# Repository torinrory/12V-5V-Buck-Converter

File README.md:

# 12V-to-5V 3A Synchronous DC-DC Buck Converter (TPS54302)

**Author:** Torin Hamilton  
**CAD Tool:** KiCad 10.0  
**Topology:** Fixed-Frequency ($400\text{ kHz}$) Peak-Current-Mode Synchronous Buck Converter  
**Board Dimensions:** $45\text{ mm} \times 30\text{ mm}$, 2-Layer FR-4 ($1.6\text{ mm}$ thickness, $1\text{ oz}$ copper)

*Rev 1.1 (3D render).*

*Rev 1.1 (2D layout).*

<details>
<summary>Rev 1.0 renders (first PCB, as fabricated)</summary>

</details>

## Revision History

| Rev | Status | Summary |
| :-: | :--- | :--- |
| **1.0** | PCBs and components ordered; awaiting assembly and bring-up | First PCB design. Component values follow TI's 5 V, 3 A reference design (Datasheet Figure 7-1). Post-layout review findings are documented in [Section 6](#6-known-issues--rev-11-changes). |
| **1.1** | PCBs ordered from OSH Park and components ordered from Mouser (Nov 2026); awaiting assembly and bring-up | Addresses all eight Rev 1.0 issues in [Section 6](#6-known-issues--rev-11-changes): shortened input hot loop with dedicated `GND` vias, solid SMD ground connections and 32 `GND` stitching vias, input damping capacitor `C7`, compact feedback network, extended `L1` pad, reduced `SW` copper, and Keystone-compatible test points. |

---

## 1. Project Overview

This project implements a compact, high-efficiency **12V-to-5V, 3A Synchronous Step-Down (Buck) DC-DC Converter** based on the Texas Instruments **`TPS54302`** (`SOT-23-6`). It is designed for 12V/24V distributed power buses, embedded systems, and benchtop prototyping, with all surface-mount and through-hole footprints selected and spaced for reliable hand-soldering and oscilloscope characterization.

### Key Electrical Specifications

| Parameter | Symbol | Value | Notes |
| :--- | :---: | :---: | :--- |
| **Input Voltage Range** | $V_{\text{IN}}$ | $8\text{ V} \text{ to } 28\text{ V}$ | Optimized for $12\text{ V}$ nominal; matches TI reference design (Datasheet Table 7-1) |
| **Output Voltage** | $V_{\text{OUT}}$ | $5.08\text{ V}$ ($5.0\text{ V}$ nom) | Set by $1\%$ feedback divider ($R_2, R_3$); $\approx 4.9\text{ -- } 5.25\text{ V}$ worst case over $V_{\text{ref}}$ ($0.581\text{ -- }0.611\text{ V}$) and resistor tolerance |
| **Max Continuous Output Current** | $I_{\text{OUT(MAX)}}$ | $3.0\text{ A}$ | Integrated $85\text{ m}\Omega$ HS / $40\text{ m}\Omega$ LS MOSFETs |
| **Switching Frequency** | $f_{\text{SW}}$ | $400\text{ kHz}$ | With $\pm 6\%$ frequency spread-spectrum for EMI reduction |
| **Peak Efficiency** | $\eta$ | $\approx 93\% \text{ -- } 95\%$ | At $V_{\text{IN}} = 12\text{ V}, V_{\text{OUT}} = 5\text{ V}$ |
| **Output Voltage Ripple** | $\Delta V_{\text{OUT}}$ | $< 30\text{ mV}_{\text{PP}}$ | Low-ESR MLCC output filter ($2 \times 22\,\mu\text{F}$) |
| **Transient Response ($1.5\text{ A}$ step)** | $\Delta V_{\text{TR}}$ | $< \pm 5\%$ ($\pm 250\text{ mV}$) | Phase-margin boosted via $75\text{ pF}$ feedforward cap |

### Repository Contents
- **[fab/rev1.0/](fab/rev1.0/)** — Rev 1.0 fabrication snapshot, exactly as ordered:
  - [Schematic PDF](fab/rev1.0/12V_5V_Buck_Converter_rev1.0_schematic.pdf) with engineering callouts
  - [Gerber & drill package (.zip)](fab/rev1.0/12V_5V_Buck_Converter_rev1.0_gerbers.zip) and [individual files](fab/rev1.0/gerbers/) (RS-274X Gerbers, Excellon drill)
  - [BOM as ordered](fab/rev1.0/12V_5V_Buck_Converter_rev1.0_BOM.xlsx)
- **[fab/rev1.1/](fab/rev1.1/)** — Rev 1.1 fabrication package:
  - [Schematic PDF](fab/rev1.1/12V_5V_Buck_Converter_rev1.1_schematic.pdf)
  - [Gerber & drill package (.zip)](fab/rev1.1/12V_5V_Buck_Converter_rev1.1_gerbers.zip) and [individual files](fab/rev1.1/gerbers/) (RS-274X Gerbers, Excellon drill)
  - [BOM](fab/rev1.1/12V_5V_Buck_Converter_rev1.1_BOM.xlsx)
- **KiCad source (always the latest revision; currently Rev 1.1):**
  - [12V_5V_Buck_Converter.kicad_sch](12V_5V_Buck_Converter.kicad_sch): KiCad 10 schematic (Rev 1.0 passed with 0 ERC violations)
  - [12V_5V_Buck_Converter.kicad_pcb](12V_5V_Buck_Converter.kicad_pcb): KiCad 10 2-layer PCB layout (0 DRC violations)
  - [Library.pretty/](Library.pretty/) + [fp-lib-table](fp-lib-table): project footprint library (`L1` extended-pad footprint)
- **[BOM.xlsx](BOM.xlsx)** — Current (Rev 1.1) orderable Bill of Materials with Manufacturer Part Numbers; the Rev 1.0 order record is kept on a separate sheet
- **[images/](images/)** — PCB renders, named by revision
- **[docs/](docs/)** — Reference datasheets (TI TPS54302)

---

## 2. Engineering Design & Component Calculations

All component values are derived from the [Texas Instruments TPS54302 Datasheet](docs/tps54302.pdf) (Section 7.2, Pages 14–18).

### 2.1 Output Voltage Set Point ($R_2, R_3$)
The `TPS54302` regulates the feedback pin (`FB`, Pin 4) to an internal bandgap reference of $V_{\text{ref}} = 0.596\text{ V}$ (typical). Using $R_2 = 100\text{ k}\Omega$ ($1\%$) for the upper divider resistor and $R_3 = 13.3\text{ k}\Omega$ ($1\%$) for the lower divider resistor:

$$V_{\text{OUT}} = V_{\text{ref}} \times \left(1 + \frac{R_2}{R_3}\right) = 0.596\text{ V} \times \left(1 + \frac{100\text{ k}\Omega}{13.3\text{ k}\Omega}\right) = 5.077\text{ V}$$

A $49.9\,\Omega$ resistor ($R_1$) is placed in series between $V_{\text{OUT}}$ and the top of the feedback network to provide an injection point for control-loop Bode plot / stability measurements.

### 2.2 Programmable Input Undervoltage Lockout ($R_4, R_5$)
Resistors $R_4 = 511\text{ k}\Omega$ ($1\%$) and $R_5 = 105\text{ k}\Omega$ ($1\%$) form an external voltage divider on the `EN` pin (Pin 5) working with the internal pull-up current ($I_p = 0.7\,\mu\text{A}$) and hysteresis current ($I_h = 1.55\,\mu\text{A}$) to prevent brownout chatter during startup and shutdown:
- **Rising Turn-On Threshold ($V_{\text{EN(rising)}} = 1.23\text{ V}$):**
  $$V_{\text{START}} = V_{\text{EN(rising)}} \left(1 + \frac{R_4}{R_5}\right) - I_p R_4 \approx 6.86\text{ V}$$
- **Falling Turn-Off Threshold ($V_{\text{EN(falling)}} = 1.16\text{ V}$):**
  $$V_{\text{STOP}} = V_{\text{EN(falling)}} \left(1 + \frac{R_4}{R_5}\right) - (I_p + I_h) R_4 \approx 5.65\text{ V}$$

### 2.3 Output Inductor Selection ($L_1$)
For a target inductor ripple ratio $K_{\text{IND}} = 0.35$ up to $V_{\text{IN(MAX)}} = 28\text{ V}$ at $f_{\text{SW}} = 400\text{ kHz}$:

$$L_{\text{MIN}} = \frac{V_{\text{OUT}} \times (V_{\text{IN(MAX)}} - V_{\text{OUT}})}{V_{\text{IN(MAX)}} \times K_{\text{IND}} \times I_{\text{OUT}} \times f_{\text{SW}}} = \frac{5 \times (28 - 5)}{28 \times 0.35 \times 3 \times 400\times 10^3} = 9.78\,\mu\text{H}$$

Selecting the standard value **$L_1 = 10\,\mu\text{H}$** (`Bourns SRP7028A-100M`):
- **Inductor Ripple Current at $V_{\text{IN}} = 12\text{ V}$:**
  $$\Delta I_L = \frac{V_{\text{OUT}} \times (V_{\text{IN}} - V_{\text{OUT}})}{V_{\text{IN}} \times L_1 \times f_{\text{SW}}} = \frac{5 \times (12 - 5)}{12 \times 10\,\mu\text{H} \times 400\text{ kHz}} = 0.729\text{ A}_{\text{PP}}$$
- **Peak Inductor Current ($I_{L(\text{PK})}$):**
  $$I_{L(\text{PK})} = I_{\text{OUT(MAX)}} + \frac{\Delta I_L}{2} \approx 3.36\text{ A} \quad (\text{ at } 12\text{ V}) \quad / \quad 3.51\text{ A} \quad (\text{ at } 28\text{ V})$$
- **Selected Inductor Margins:** The `Bourns SRP7028A-100M` shielded power inductor is rated for **$I_{\text{RMS}} = 3.5\text{ A}$** and **$I_{\text{sat}} = 6.0\text{ A}$** (DCR $75\text{ m}\Omega$ typ / $85\text{ m}\Omega$ max, Bourns datasheet). That gives about $1.7\times$ saturation margin over the $3.51\text{ A}$ worst-case peak current (at $28\text{ V}$ input) and about $17\%$ headroom between the $3.5\text{ A}$ RMS rating and the $3.0\text{ A}$ maximum continuous output current.

### 2.4 Input & Output Capacitor Selection ($C_1\text{--}C_7$)
- **Input Decoupling ($C_1 = 10\,\mu\text{F}, 50\text{ V}$ & $C_2 = 0.1\,\mu\text{F}, 50\text{ V X7R}$):**
  - Worst-case input RMS ripple current is $I_{\text{CIN(RMS)}} \approx I_{\text{OUT(MAX)}} / 2 = 1.5\text{ A}$.
  - $C_1$ ($1206$ package, $50\text{ V}$ X5R/X7R) provides bulk charge storage with minimal DC-bias derating at $12\text{ V}$, while $C_2$ ($0805$) is placed immediately adjacent to `U1` Pin 3 (`VIN`) and Pin 1 (`GND`) to shunt high-$di/dt$ switching currents.
- **Input Damping Capacitor ($C_7 = 47\,\mu\text{F}, 50\text{ V}$ aluminum electrolytic, added in Rev 1.1):**
  - Ceramic-only input capacitance and the supply-lead inductance form a lightly damped LC that can ring toward $2 \times V_{\text{IN}}$ when the board is connected to a live supply. `C7` provides roughly $6\times$ the effective ceramic input capacitance, and its ESR ($\sim 0.5\text{ -- }1\,\Omega$, comparable to the LC characteristic impedance) damps the ringing. At $400\text{ kHz}$ the switching ripple still flows almost entirely through the ceramics.
- **Bootstrap Capacitor ($C_3 = 0.1\,\mu\text{F}, 50\text{ V X7R}$):**
  - Connected between `BOOT` (Pin 6) and `SW` (Pin 2) to supply the floating gate drive for the integrated high-side N-channel MOSFET.
- **Output Filter Capacitors ($C_4, C_5 = 2 \times 22\,\mu\text{F}, 25\text{ V X5R/X7R}$):**
  - To contain a $1.5\text{ A}$ load transient within $\Delta V_{\text{OUT}} = \pm 5\%$ ($0.25\text{ V}$), the minimum required effective output capacitance is:
    $$C_{\text{OUT(MIN)}} > \frac{2 \times \Delta I_{\text{OUT}}}{f_{\text{SW}} \times \Delta V_{\text{OUT}}} = \frac{2 \times 1.5\text{ A}}{400\text{ kHz} \times 0.25\text{ V}} = 30\,\mu\text{F}$$
  - Using two parallel $22\,\mu\text{F}$, $25\text{ V}$ `1206` ceramic capacitors ($44\,\mu\text{F}$ nominal) accounts for MLCC DC-bias derating at $5\text{ V}$ while halving equivalent series resistance (ESR) and ESL.
- **Feedforward Compensation Capacitor ($C_6 = 75\text{ pF}, 50\text{ V C0G/NP0}$):**
  - Placed in parallel with $R_2$ to introduce a phase-lead zero near the control loop crossover frequency ($f_0 \approx \frac{5.1}{V_{\text{OUT}} \times C_{\text{OUT}}} \approx 23\text{ kHz}$), boosting phase margin with low-ESR ceramic output capacitors:
    $$C_6 \approx \frac{1}{2\pi f_0 R_2} \approx 75\text{ pF}$$

---

## 3. PCB Layout & EMI Mitigation Architecture

Switching regulators involve high-$di/dt$ current loops ($400\text{ kHz}$ square-wave switching up to $3\text{ A}$). The 2-layer PCB ([12V_5V_Buck_Converter.kicad_pcb](12V_5V_Buck_Converter.kicad_pcb)) follows Texas Instruments' layout guidelines (Datasheet Section 7.4). This section describes the **Rev 1.1** layout; the Rev 1.0 layout and its issues are documented in [Section 6](#6-known-issues--rev-11-changes).

1. **Short Input Hot Loop:** `C2` ($0.1\,\mu\text{F}$) sits $\approx 2\text{ mm}$ from `U1` Pin 3 (`VIN`), with `C1` ($10\,\mu\text{F}$) directly behind it. Because the `SW` trace leaving Pin 2 must split the top-layer pour between the capacitors and Pin 1, the `GND` return is made through the bottom plane: three `GND` vias at the `C1`/`C2` ground pads and two at `U1` Pin 1 keep the loop to a few millimeters.
2. **Compact Switching Node (`SW`):** `L1` is rotated so its `SW` pad faces `U1`, and bootstrap capacitor `C3` sits directly on the `SW` path between `L1` and `U1` with a $\approx 3\text{ mm}$ `BOOT` trace to Pin 6. Test point `TP2` is a $1.5\text{ mm}$ top-layer pad on a $0.3\text{ mm}$ trace, so no high-current-width copper or plated hole is added to the `SW` node.
3. **High-Current Power Routing with Pin Neck-Down:** `Vin`, `SW`, and `Vout` use $1.5\text{ mm}$ tracks, necking down to $0.5\text{ mm}$ only for the last $\approx 1.5\text{ mm}$ into the fine-pitch ($0.95\text{ mm}$) `SOT-23-6` pads.
4. **Compact Feedback Network:** `R2`, `R3`, and `C6` are grouped at `U1` Pin 4 on the side away from `L1` and `SW`; the high-impedance `FB` node is entirely on `F.Cu` ($\approx 4\text{ mm}$ to `R3`, $4\text{ mm}$ across the divider). The longer run is on the low-impedance sense side: `R1` taps `Vout` at output capacitor `C4`.
5. **Output Filter Placement:** `L1` feeds `C4`/`C5` before the output connector `J2`, so the load sees filtered output.
6. **Input Damping:** Electrolytic `C7` sits in-line on the `Vin` trace between `J1` and the ceramic input capacitors.
7. **Ground Planes, Vias & Thermal Path:** Both `F.Cu` and `B.Cu` are poured with `GND` (`0.3 mm` clearance). SMD pads connect solidly to the pour (zone setting *Reliefs for PTH*) for low inductance and heat spreading from `U1`; through-hole pads keep thermal reliefs for hand soldering. 32 `GND` vias, at the critical capacitor and IC ground pads plus a $\approx 6\text{ mm}$ stitching pattern, tie the layers together. The bottom plane is unbroken under the power stage.
8. **Test Points:** `TP1` (`Vin`), `TP3` (`Vout`), and `TP4` (`GND`) use Keystone 5005 compact loops ($1.6\text{ mm}$ holes). `TP4` sits $4\text{ mm}$ from `TP3` for a scope ground-spring ripple measurement.

---

## 4. Bill of Materials (BOM)

The full Rev 1.1 spreadsheet is available in [BOM.xlsx](BOM.xlsx) (the Rev 1.0 order record is on its own sheet and in [fab/rev1.0/](fab/rev1.0/)).

| Ref | Qty | Value | Package | Manufacturer | MPN | Description |
| :--- | :-: | :--- | :--- | :--- | :--- | :--- |
| `U1` | 1 | `TPS54302` | `SOT-23-6` | Texas Instruments | `TPS54302DDCT` | 4.5V–28V In, 3A Sync Buck Converter (`DDCR` is the same part on a larger reel) |
| `L1` | 1 | `10uH` | `7.3x6.6mm` | Bourns | `SRP7028A-100M` | Shielded Power Inductor, $3.5\text{ A}_{\text{RMS}}$, $6\text{ A}_{\text{sat}}$, $85\text{ m}\Omega$ max DCR (custom footprint, `Vout` pad extended $1\text{ mm}$ for hand soldering) |
| `C1` | 1 | `10uF` | `1206` | Murata | `GRT31CR61H106KE01L` | MLCC $10\,\mu\text{F}$, $50\text{ V}$, X5R, $\pm 10\%$. **Rev 1.0 as built:** out-of-stock substitute Murata `GRM31CR71E106MA12L` ($25\text{ V}$) — see bench input-voltage limit in Section 5 |
| `C2, C3` | 2 | `0.1uF` | `0805` | Yageo | `CC0805KRX7R9BB104` | MLCC $0.1\,\mu\text{F}$, $50\text{ V}$, X7R, $\pm 10\%$ |
| `C4, C5` | 2 | `22uF` | `1206` | Samsung | `CL31A226KAHNNNE` | MLCC $22\,\mu\text{F}$, $25\text{ V}$, X5R, $\pm 10\%$ |
| `C6` | 1 | `75pF` | `0805` | Yageo | `CC0805JRNPO9BN750` | MLCC $75\text{ pF}$, $50\text{ V}$, C0G/NP0, $\pm 5\%$ |
| `C7` | 1 | `47uF` | Radial $8 \times 11\text{ mm}$, $3.5\text{ mm}$ pitch | KEMET | `ESH476M050AG3KA` | Aluminum electrolytic $47\,\mu\text{F}$, $50\text{ V}$, $105\,{}^{\circ}\text{C}$ — input damping (Rev 1.1) |
| `R1` | 1 | `49.9` | `0805` | Yageo | `RC0805FR-0749R9L` | Thick Film Resistor $49.9\,\Omega$, $1\%$, $1/8\text{ W}$ |
| `R2` | 1 | `100k` | `0805` | Yageo | `RC0805FR-07100KL` | Thick Film Resistor $100\text{ k}\Omega$, $1\%$, $1/8\text{ W}$ |
| `R3` | 1 | `13.3k` | `0805` | Yageo | `RC0805FR-0713K3L` | Thick Film Resistor $13.3\text{ k}\Omega$, $1\%$, $1/8\text{ W}$ |
| `R4` | 1 | `511k` | `0805` | Yageo | `RC0805FR-07511KL` | Thick Film Resistor $511\text{ k}\Omega$, $1\%$, $1/8\text{ W}$ |
| `R5` | 1 | `105k` | `0805` | Yageo | `RC0805FR-07105KL` | Thick Film Resistor $105\text{ k}\Omega$, $1\%$, $1/8\text{ W}$ |
| `R6` | 1 | `1k` | `0805` | Yageo | `RC0805FR-071KL` | Thick Film Resistor $1\text{ k}\Omega$, $1\%$, $1/8\text{ W}$ |
| `D1` | 1 | `Green` | `0805` | Lite-On | `LTST-C170KGKT` | Green SMD LED ($571\text{ nm}, V_F = 2.0\text{ V}$) |
| `J1, J2` | 2 | `Screw Term` | `1x02 P5.08mm` | Phoenix Contact | `1715721` | 2-Pin Terminal Block, $5.08\text{ mm}$, $17.5\text{ A}$ |
| `TP1, TP3, TP4` | 3 | `Test Point` | Keystone compact, $1.6\text{ mm}$ hole | Keystone | `5005` | Compact test point loop (`Vin`, `Vout`, `GND`) |
| `TP2` | — | `Test Pad` | $1.5\text{ mm}$ SMD pad | — | DNP (bare pad) | `SW` probe point; no part installed |

---

## 5. Hand-Soldering & Bench Bring-Up Guide

### Recommended Soldering Order (Lowest to Highest Profile)
1. **Regulator IC (`U1` - `TPS54302`):** Verify the Pin 1 dot/bevel aligns with the top-left pad (`GND`, marked by the silkscreen triangle). Tack one corner pin with flux and fine solder, verify alignment, then solder the remaining 5 pins.
2. **0805 Passives & LED (`C2`, `C3`, `C6`, `R1`–`R6`, `D1`):** Note that `D1` is polarized—align the green cathode marking on the LED with **Pad 1 (`GND`, left pad)**.
3. **1206 Input/Output Capacitors (`C1`, `C4`, `C5`).**
4. **Power Inductor (`L1` - `SRP7028A-100M`):** Pre-tin both pads. Place `L1`, then heat the extended `Vout` pad (Rev 1.1) with the iron until the solder underneath reflows and the part seats. Reflow the `SW` side with hot air, or with the iron and flux on the exposed pad edge.
5. **Through-Hole Parts (`J1`, `J2`, `C7`, `TP1`, `TP3`, `TP4`):** These pads tie into two layers of `GND` pour — raise the iron temperature and allow extra dwell time on the `GND` pins. `C7` is polarized: its `+` lead goes to the square pad (`Vin`).

### Bench Equipment
Bring-up and characterization use only a **current-limited bench DC power supply** and a **digital multimeter (DMM)**. Load is provided by a resistor load bank: six TE Connectivity `SQPW1010RJ` ($10\,\Omega$, $10\text{ W}$ axial wirewound) resistors on a TE/Buchanan `1546671-8` 8-position dual-row barrier strip. Alternate positions are tied together with 18 AWG jumpers to form `Vout` and `GND` buses, and each resistor bridges two adjacent positions. Each connected resistor adds $0.5\text{ A}$ at $5\text{ V}$ ($2.5\text{ W}$ per resistor); all six give $1.67\,\Omega$ = $3\text{ A}$. Connect it to `J2` with 18–20 AWG leads, and keep the hot resistor bodies clear of the plastic strip.

> **⚠ Rev 1.0 input-voltage limit:** The Rev 1.0 build uses a $25\text{ V}$-rated substitute for `C1` (the specified $50\text{ V}$ part was out of stock; Rev 1.1 specifies a $50\text{ V}$ part). Limit bench testing to **$\leq 15\text{ V}$ input** until `C1` is replaced with a $50\text{ V}$ $10\,\mu\text{F}$ capacitor. The $24\text{ V}$ and $28\text{ V}$ rows in the Section 5.5 results table apply only after that replacement.

### 5.1 Power-Off Checks
| Measurement (DMM) | Expected | Fault Indication |
| :--- | :--- | :--- |
| `J1` resistance (`Vin` to `GND`) | Rises as `C1` charges, settles in the hundreds of kΩ ($R_4 + R_5 \approx 616\text{ k}\Omega$) | $< 100\,\Omega$ → solder bridge / reversed part |
| `J2` resistance (`Vout` to `GND`) | $\approx 113\text{ k}\Omega$ ($R_1 + R_2 + R_3$), may read lower through `D1` | $< 100\,\Omega$ → solder bridge |
| `TP2` (`SW`) diode mode to `GND` and to `Vin` | One diode drop ($\approx 0.3\text{ -- }0.7\text{ V}$) in one direction | $\approx 0\text{ V}$ → `SW` shorted |
| `D1` diode mode | LED glows faintly | No glow → `D1` reversed or open |

### 5.2 No-Load Power-Up
1. Set the supply to **$12.0\text{ V}$** with a **$100\text{ mA}$** current limit and connect to `J1`.
2. `D1` should illuminate after the internal $5\text{ ms}$ soft start.
3. Input current should be only a few mA — mostly the LED ($\approx 3\text{ mA}$ at $5\text{ V}$ out, $\approx 1.5\text{ mA}$ at $12\text{ V}$ in), since Eco-mode pulse skipping keeps quiescent losses low.
4. `TP3` (`Vout`) to `TP4` (`GND`) should read **$\approx 4.9\text{ -- }5.25\text{ V}$** ($5.08\text{ V}$ nominal). Record the actual value; a reading anywhere in this window is within datasheet tolerance.

### 5.3 UVLO Threshold Verification
1. Starting at $0\text{ V}$, slowly raise the supply while monitoring `Vout`. Record the input voltage at which the output turns on (**expected $\approx 6.86\text{ V}$**).
2. Slowly lower the supply and record the input voltage at which the output drops out (**expected $\approx 5.65\text{ V}$**).

### 5.4 Switching Frequency (DMM Hz mode)
With $\geq 0.5\text{ A}$ of load applied (Eco-mode pulse skipping makes light-load readings low or unstable), measure `TP2` (`SW`) to `GND` in frequency mode. Expect **$\approx 400\text{ kHz}$**, varying by up to $\pm 6\%$ due to spread spectrum.

### 5.5 Load Regulation, Line Regulation & Efficiency
1. Raise the supply current limit to **$2.0\text{ A}$**.
2. Measure `Vout` directly across `C4`/`C5` (not at the load resistors) and `Vin` at `TP1`/`TP4`. Measure $I_{\text{OUT}}$ on the DMM's 10 A range in series with the load (or compute $V_{\text{OUT}} / R_{\text{LOAD}}$) and take $I_{\text{IN}}$ from the supply readout or DMM.
3. Step the load in $0.5\text{ A}$ increments at $V_{\text{IN}} = 8, 12, 24, 28\text{ V}$ and compute $\eta = \dfrac{V_{\text{OUT}} I_{\text{OUT}}}{V_{\text{IN}} I_{\text{IN}}}$.
4. Allow `U1` to settle thermally at each step above $2\text{ A}$. At $3\text{ A}$ the IC dissipates $\approx 0.6\text{ -- }0.7\text{ W}$; with $R_{\theta JA}$ between $57\,{}^{\circ}\text{C/W}$ (TI EVM) and $119\,{}^{\circ}\text{C/W}$ (JEDEC), a $50\text{ -- }80\,{}^{\circ}\text{C}$ rise is expected. If the output cycles off at full load, suspect thermal shutdown ($160\,{}^{\circ}\text{C}$).

| $V_{\text{IN}}$ (V) | $I_{\text{IN}}$ (A) | $V_{\text{OUT}}$ (V) | $I_{\text{OUT}}$ (A) | $P_{\text{IN}}$ (W) | $P_{\text{OUT}}$ (W) | $\eta$ (%) |
| :---: | :---: | :---: | :---: | :---: | :---: | :---: |
| 12 | | | 0.0 | | | — |
| 12 | | | 0.5 | | | |
| 12 | | | 1.0 | | | |
| 12 | | | 1.5 | | | |
| 12 | | | 2.0 | | | |
| 12 | | | 2.5 | | | |
| 12 | | | 3.0 | | | |
| 8 | | | 3.0 | | | |
| 24 | | | 3.0 | | | |
| 28 | | | 3.0 | | | |

### 5.6 Short-Circuit / Hiccup Protection (Optional)
With the supply limited to $\approx 1\text{ A}$, short `J2`. Average input current should remain low as the device enters hiccup mode (shutdown after 512 overcurrent cycles, restart after 16,384 cycles). Remove the short and confirm `Vout` recovers automatically.

### 5.7 Output Ripple (Oscilloscope Required)
A DMM's AC mode lacks the bandwidth to measure $400\text{ kHz}$ ripple. If an oscilloscope is available, AC-couple a probe with a short ground spring and verify $< 30\text{ mV}_{\text{PP}}$ ripple. On **Rev 1.1**, place the probe tip on `TP3` (`Vout`) and the ground spring on `TP4` (`GND`), $4\text{ mm}$ apart. On **Rev 1.0**, `TP3` and `TP4` are too far apart, so probe directly across `C5`.

---

## 6. Known Issues & Rev 1.1 Changes

A post-layout review of Rev 1.0 (direct inspection of the `.kicad_pcb` copper, zone fills, and via placement) found the following. Component values match TI's 5 V, 3 A reference design (Datasheet Figure 7-1, Table 7-2) exactly; the items below concern PCB layout and operating practice. None are expected to prevent regulation at $12\text{ V}$ input; they affect switching-node ringing, EMI, and thermal margin.

**Status:** ✅ All eight issues are fixed in the Rev 1.1 layout. These are design changes that have not yet been fabricated or bench-verified.

| # | Status | Issue (Rev 1.0) | Impact | Rev 1.0 Bench Workaround | Rev 1.1 Change |
| :-: | :-: | :--- | :--- | :--- | :--- |
| 1 | ✅ | **Enlarged input hot loop.** The `SW` trace leaving Pin 2 splits the top `GND` pour between `C2` and `U1` Pin 1, leaving Pin 1 on a small isolated top-copper island tied to the bottom plane by one via. The bottom-layer `GND` trace intended to link them terminates under `C2`'s top-side pad with no via, so it connects nothing. The actual `C2` return path runs through `J1`'s `GND` pin or the `C5` via and back through the bottom plane — roughly $35\text{ mm}$ versus a target of $< 5\text{ mm}$. DRC does not flag this because the net is connected through the pours. | Increased `SW` ringing/overshoot and radiated EMI; reduced `SW` voltage margin at $24\text{ -- }28\text{ V}$ input ($30\text{ V}$ abs. max) | Solder a short insulated jumper wire from `C2`'s `GND` pad directly to `U1` Pin 1, passing over the solder-masked `SW` trace | Place `C2` directly across Pins 3 and 1 with its `GND` pad on the same copper as Pin 1; add `GND` vias at the `C2` and `C1` ground pads; route `SW` so it does not bisect the input `GND` return **Done:** `C2` moved to $\approx 2\text{ mm}$ from Pin 3; three `GND` vias at the `C1`/`C2` ground pads and two at `U1` Pin 1 give a return path of a few millimeters through the bottom plane. |
| 2 | ✅ | **Limited thermal path for `U1`.** `0.3 mm` thermal-relief spokes and only two board-wide `GND` vias restrict heat spreading from the `SOT-23-6` pins. | Higher junction temperature at $3\text{ A}$ ($\approx 0.6\text{ -- }0.7\text{ W}$ dissipation); possible thermal shutdown ($160\,{}^{\circ}\text{C}$) at full load | Step load gradually and monitor `U1` temperature; derate continuous current if the output cycles off | Solid (no-spoke) pad connections for `U1` `GND` and power-capacitor `GND` pads; add a via stitching array around `U1` and the input/output capacitors **Done:** zone pad connection set to *Reliefs for PTH* — all SMD `GND` pads connect solidly while through-hole pads keep reliefs for solderability; 32 `GND` vias (critical-pad vias plus $\approx 6\text{ mm}$ stitching) tie the planes together. |
| 3 | ✅ | **Hot-plug input overshoot.** Ceramic-only input capacitance with lead inductance forms an underdamped LC that can ring toward $2 \times V_{\text{IN}}$ when connected to a live supply. | Safe at $12\text{ V}$ ($\approx 24\text{ V}$ peak); can exceed the $30\text{ V}$ `VIN` absolute maximum at $\geq 16\text{ V}$ input | Connect leads first, then enable the supply output | Add a damping bulk aluminum electrolytic (e.g., $47\,\mu\text{F}$, $50\text{ V}$) at `J1` **Done:** `C7`, KEMET `ESH476M050AG3KA` ($47\,\mu\text{F}$, $50\text{ V}$ aluminum electrolytic), placed in-line on the `Vin` trace at `J1`. |
| 4 | ✅ | **Long `FB` trace.** The high-impedance `FB` node runs $\approx 10\text{ mm}$ with two vias before reaching `R2`/`C6`. | Low risk (routed clear of `SW`); increased noise pickup susceptibility | — | Place `R2`, `R3`, and `C6` immediately adjacent to Pin 4; keep `FB` on one layer **Done:** `R2`, `R3`, and `C6` grouped at Pin 4; `FB` routed entirely on `F.Cu`; the `B.Cu` jumper and both `FB` vias removed. The longer run is now the low-impedance `R1` sense trace from `C4`. |
| 5 | ✅ | **`L1` hand-solderability.** `SRP7028A` terminals sit mostly beneath the inductor body. | Difficult to solder with an iron alone | Use hot air or a hot plate; pre-tin pads | Use extended-pad footprint variant **Done:** custom project-library footprint with the `Vout` pad extended $1\text{ mm}$ outward (inner edge unchanged). The `SW` pad is left at standard size to avoid adding switching-node copper next to `C3`. |
| 6 | ✅ | **Excess `SW` copper area.** A $6.2\text{ mm} \times 1.5\text{ mm}$ `SW` branch runs to bootstrap cap `C3` (followed by a $5\text{ mm}$ `BOOT` return to Pin 6), and a $6.8\text{ mm} \times 1.5\text{ mm}$ stub runs to `TP2`. Neither carries significant current. | The `SW` node swings $0 \leftrightarrow V_{\text{IN}}$ at $400\text{ kHz}$; extra copper increases capacitively coupled and radiated EMI | — | Place `C3` directly beside `U1` between Pins 2 and 6 with short $0.3\text{ -- }0.5\text{ mm}$ traces; narrow the `TP2` stub to $0.3\text{ mm}$ or relocate `TP2` adjacent to `L1` Pad 1 **Done:** `L1` rotated so its `SW` pad faces `U1`; `C3` placed on the `SW` path between `L1` and `U1` ($\approx 3\text{ mm}$ `BOOT` trace); `TP2` changed to a $1.5\text{ mm}$ SMD pad on a $0.3\text{ mm}$ trace. |
| 7 | ✅ | **Long necked-down power traces.** `SW` runs $\approx 5\text{ mm}$ at $0.5\text{ mm}$ from Pin 2 toward `L1` (full $3\text{ A}$), and `VIN` runs $\approx 4\text{ mm}$ at $0.5\text{ mm}$ from `C2` to Pin 3. | Added resistance and inductance in the main power path | — | Neck down to $0.5\text{ mm}$ only at the `SOT-23-6` pads, widening to $1\text{ -- }1.5\text{ mm}$ immediately (or use small copper pours for `VIN`/`SW`/`Vout`) **Done:** `SW` and `VIN` neck down to $0.5\text{ mm}$ for only $\approx 1.5\text{ mm}$ at the pins, then run at $1.5\text{ mm}$. |
| 8 | ✅ | **Output capacitors placed after the load connector.** `Vout` routes `L1` → `TP3` → `J2` → `C4`/`C5` ($\approx 38\text{ mm}$ total), so the output filter sits at the far end of the path. | Higher ripple at `J2`; larger output current loop | Measure ripple across `C5`, not at `J2` | Place `C4`/`C5` immediately at `L1` Pad 2, then route to `J2`; keep `R1` sensing at the capacitors **Done:** `L1` now feeds `C4`/`C5` before `J2`, and `R1` senses at `C4`. The $\approx 16\text{ mm}$ trace from `L1` to the capacitors was kept: it carries continuous inductor current (DC plus triangular ripple), so its length has negligible effect. |

### Additional Rev 1.1 Changes
- **Test points:** `TP1`, `TP3`, and `TP4` changed to the Keystone 5005 compact footprint ($1.6\text{ mm}$ hole); the Rev 1.0 $0.7\text{ mm}$ holes did not fit the specified test point. `TP4` (`GND`) moved to $4\text{ mm}$ from `TP3` (`Vout`) for scope ground-spring ripple measurements.
- **`C1`:** specified as a $50\text{ V}$ part (Murata `GRT31CR61H106KE01L`) to support the full $8\text{ -- }28\text{ V}$ input range.
- **Silkscreen:** input labeled `8-28V`; board revision text updated to Rev 1.1.

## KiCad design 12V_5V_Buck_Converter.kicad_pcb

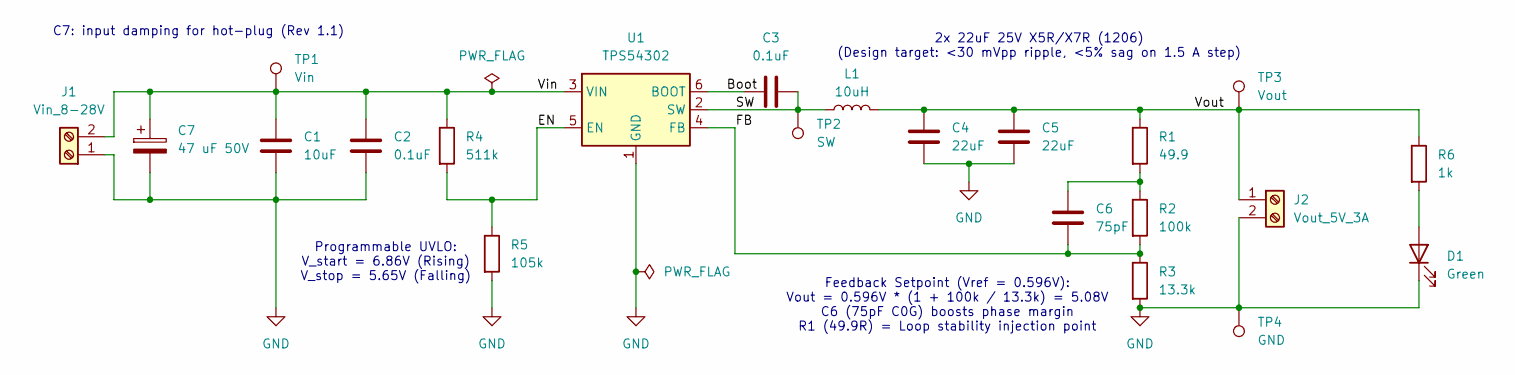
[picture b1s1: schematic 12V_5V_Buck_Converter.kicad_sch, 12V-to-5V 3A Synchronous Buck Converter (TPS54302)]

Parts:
C1: 10uF; C_1206_3216Metric_Pad1.33x1.80mm_HandSolder
C2, C3: 0.1uF; C_0805_2012Metric_Pad1.18x1.45mm_HandSolder
C4, C5: 22uF; C_1206_3216Metric_Pad1.33x1.80mm_HandSolder
C6: 75pF; C_0805_2012Metric_Pad1.18x1.45mm_HandSolder
C7: 47 uF 50V; CP_Radial_D8.0mm_P3.50mm
D1: Green; LED_0805_2012Metric_Pad1.15x1.40mm_HandSolder
J1: Vin_8-28V; TerminalBlock_Phoenix_MKDS-1,5-2-5.08_1x02_P5.08mm_Horizont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
J2: Vout_5V_3A; TerminalBlock_Phoenix_MKDS-1,5-2-5.08_1x02_P5.08mm_Horizont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
L1: 10uH; L_Bourns_SRP7028A_7.3x6.6mm_Extended
R1: 49.9; R_0805_2012Metric_Pad1.20x1.40mm_HandSolder
R2: 100k; R_0805_2012Metric_Pad1.20x1.40mm_HandSolder
R3: 13.3k; R_0805_2012Metric_Pad1.20x1.40mm_HandSolder
R4: 511k; R_0805_2012Metric_Pad1.20x1.40mm_HandSolder
R5: 105k; R_0805_2012Metric_Pad1.20x1.40mm_HandSolder
R6: 1k; R_0805_2012Metric_Pad1.20x1.40mm_HandSolder
TP1: Vin; TestPoint_Keystone_5005-5009_Compact
TP2: SW; TestPoint_Pad_D1.5mm
TP3: Vout; TestPoint_Keystone_5005-5009_Compact
TP4: GND; TestPoint_Keystone_5005-5009_Compact
U1: TPS54302; SOT-23-6

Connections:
/Boot: C3.1, U1.6 (BOOT)
/EN: R4.2, R5.1, U1.5 (EN)
/FB: C6.2, R2.2, R3.1, U1.4 (FB)
/SW: C3.2, L1.1, TP2.1 (1_1), U1.2 (SW)
/Vin: C1.1, C2.1, C7.1, J1.2, R4.1, TP1.1 (1_1), U1.3 (VIN)
/Vout: C4.2, C5.1, J2.1, L1.2, R1.1, R6.1, TP3.1 (1_1)
GND: C1.2, C2.2, C4.1, C5.2, C7.2, D1.1 (K), J1.1, J2.2, R3.2, R5.2, TP4.1 (1_1), U1.1 (GND)
unnamed: C6.1, R1.2, R2.1
unnamed: D1.2 (A), R6.2

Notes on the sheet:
Programmable UVLO: V_start = 6.86V (Rising) V_stop = 5.65V (Falling)
2x 22uF 25V X5R/X7R (1206) (Design target: <30 mVpp ripple, <5% sag on 1.5 A step)
Feedback Setpoint (Vref = 0.596V): Vout = 0.596V * (1 + 100k / 13.3k) = 5.08V C6 (75pF C0G) boosts phase margin R1 (49.9R) = Loop stability injection point
C7: input damping for hot-plug (Rev 1.1)

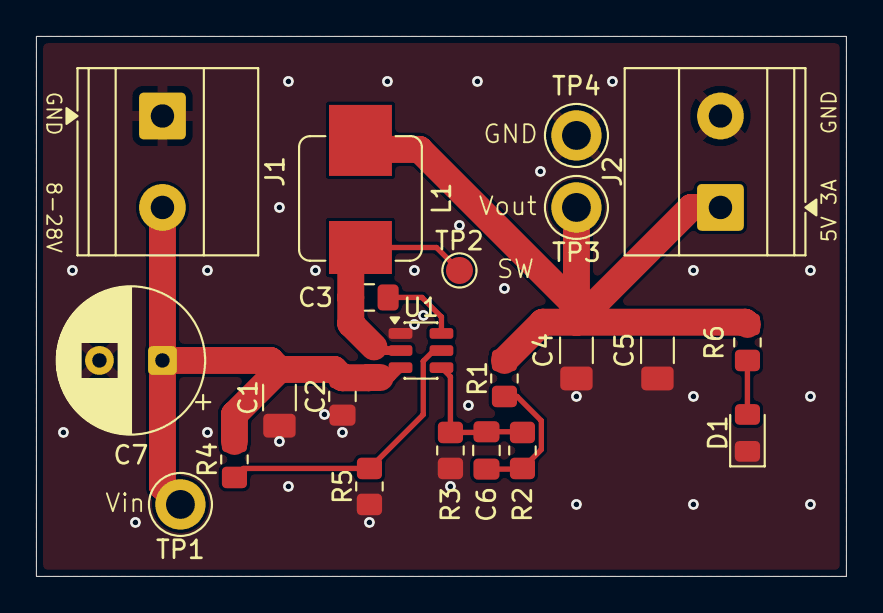
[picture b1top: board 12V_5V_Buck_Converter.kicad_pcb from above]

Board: 2 copper layers, 45.0 x 30.0 mm, 22 parts (0 on the bottom side), 9 nets.

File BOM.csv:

Item,Reference,Qty,Value,Description,Package / KiCad Footprint,Manufacturer,Manufacturer Part Number (MPN),Alternate MPN,Key Specifications & Engineering Notes
1,U1,1,TPS54302,"IC REG BUCK SYNC 5V 3A SOT23-6",Package_TO_SOT_SMD:SOT-23-6,Texas Instruments,TPS54302DDCR,TPS54302DDCT,"4.5V-28V Input, 3A Continuous Output, 400kHz Synchronous Step-Down Converter (integrated 85mOhm/40mOhm FETs)"
2,L1,1,10uH,"Shielded Molded Power Inductor 10uH 4.5A",Inductor_SMD:L_Bourns_SRP7028A_7.3x6.6mm,Bourns,SRP7028A-100M,SRP7050TA-100M,"10uH +/-20%, I_rms = 4.5A, I_sat = 8.0A, DCR = 53.5mOhm max, 7.3x6.6mm SMD"
3,C1,1,10uF,"Input Bulk Ceramic Capacitor 10uF 50V X7R",Capacitor_SMD:C_1206_3216Metric_Pad1.33x1.80mm_HandSolder,Samsung Electro-Mechanics,CL31B106KBHNNNE,GRM31CR71H106KA12L,"10uF +/-10%, 50V (exceeds TI 35V min recommendation), X7R Dielectric, 1206"
4,"C2, C3",2,0.1uF,"HF Input Bypass & Bootstrap Capacitor 0.1uF 50V X7R",Capacitor_SMD:C_0805_2012Metric_Pad1.18x1.45mm_HandSolder,Yageo,CC0805KRX7R9BB104,CL21B104KBCNNNC,"0.1uF (100nF) +/-10%, 50V, X7R Dielectric, 0805 (C2 = VIN HF Bypass, C3 = BOOT-SW Charge Pump)"
5,"C4, C5",2,22uF,"Output Filter Ceramic Capacitor 22uF 25V X5R/X7R",Capacitor_SMD:C_1206_3216Metric_Pad1.33x1.80mm_HandSolder,Murata Electronics,GRM31CR61E226KE15L,CL31A226KAHNNNE,"22uF +/-10%, 25V (minimizes DC bias derating at 5V), X5R/X7R Dielectric, 1206 (44uF nominal total)"
6,C6,1,75pF,"Feedforward Compensation Capacitor 75pF 50V C0G/NP0",Capacitor_SMD:C_0805_2012Metric_Pad1.18x1.45mm_HandSolder,Murata Electronics,GRM2165C1H750JA01D,CC0805JRNPO9BN750,"75pF +/-5%, 50V, C0G/NP0 Dielectric, 0805 (boosts control loop phase margin at crossover)"
7,R1,1,49.9,"Control Loop Injection Resistor 49.9 Ohm 1%",Resistor_SMD:R_0805_2012Metric_Pad1.20x1.40mm_HandSolder,Yageo,RC0805FR-0749R9L,CRCW080549R9FKTA,"49.9 Ohm +/-1%, 0.125W (1/8W), Thick Film, 0805 (Bode plot / stability test injection point)"
8,R2,1,100k,"Upper Feedback Divider Resistor 100k Ohm 1%",Resistor_SMD:R_0805_2012Metric_Pad1.20x1.40mm_HandSolder,Yageo,RC0805FR-07100KL,CRCW0805100KFKEA,"100k Ohm +/-1%, 0.125W (1/8W), Thick Film, 0805 (sets Vout = 5.08V with R3 = 13.3k)"
9,R3,1,13.3k,"Lower Feedback Divider Resistor 13.3k Ohm 1%",Resistor_SMD:R_0805_2012Metric_Pad1.20x1.40mm_HandSolder,Yageo,RC0805FR-0713K3L,CRCW080513K3FKEA,"13.3k Ohm +/-1%, 0.125W (1/8W), Thick Film, 0805 (sets Vout = 5.08V with R2 = 100k)"
10,R4,1,511k,"Upper UVLO Enable Divider Resistor 511k Ohm 1%",Resistor_SMD:R_0805_2012Metric_Pad1.20x1.40mm_HandSolder,Yageo,RC0805FR-07511KL,CRCW0805511KFKEA,"511k Ohm +/-1%, 0.125W (1/8W), Thick Film, 0805 (sets Vin UVLO start/stop thresholds)"
11,R5,1,105k,"Lower UVLO Enable Divider Resistor 105k Ohm 1%",Resistor_SMD:R_0805_2012Metric_Pad1.20x1.40mm_HandSolder,Yageo,RC0805FR-07105KL,CRCW0805105KFKEA,"105k Ohm +/-1%, 0.125W (1/8W), Thick Film, 0805 (sets Vin UVLO start/stop thresholds)"
12,R6,1,1k,"LED Current Limiting Resistor 1k Ohm 1%",Resistor_SMD:R_0805_2012Metric_Pad1.20x1.40mm_HandSolder,Yageo,RC0805FR-071KL,CRCW08051K00FKEA,"1k Ohm +/-1%, 0.125W (1/8W), Thick Film, 0805 (limits D1 indicator LED current to ~3mA at 5V)"
13,D1,1,Green,"5V Power Good Indicator LED Green 0805",LED_SMD:LED_0805_2012Metric_Pad1.15x1.40mm_HandSolder,Lite-On,LTST-C170KGKT,150080GS75000,"Green (571nm) SMD LED, Vf = 2.0V typ, 0805 (Note: Align cathode mark with Pad 1 / GND on PCB)"
14,"J1, J2",2,"Vin_12V, Vout_5V_3A","2-Pos Screw Terminal Block 5.08mm Pitch",TerminalBlock_Phoenix:TerminalBlock_Phoenix_MKDS-1,5-2-5.08_1x02_P5.08mm_Horizontal,Phoenix Contact,1715721,OSTTC022162,"MKDS 1,5/ 2-5,08, 2-Pin 5.08mm Pitch, Through-Hole, Rated 17.5A / 400V, 14-26 AWG"
15,"TP1, TP2, TP3, TP4",4,"Vin, SW, Vout, GND","PCB Test Point Loop (or Probe Bare PTH Directly)",TestPoint:TestPoint_THTPad_D1.5mm_Drill0.7mm,Keystone Electronics,5005,DNP (Bare Pad),"OptionalMiniature THT Test Point for 0.7mm (0.028in) drill, or leave unpopulated to probe plated holes directly"
